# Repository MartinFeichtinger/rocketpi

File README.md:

# RocketPi
The aim of this project is to controll a water rocket with a Raspberry Pi Zero.

## What is a water rocket?
A water rocket is a type of model rocket using water as its reaction mass.
The water is forced out by a pressurized gas, typically compressed air. Like all rocket engines, it operates on the principle of Newton's third law of motion.

## What's special about our water rocket?
The fuel tank consists of a plastic bottle. This bottle can withstand a maximum pressure of 9 bar.
In order to achieve a higher flight altitude, we have decided to strengthen this plastic bottle with fiber-reinforced tape.
Whith this new tank we are able to reach pressures up to 13 bar.
Futhermore a Raspberry Pi Zero is used to eject the parachute and determine the flight altitude.
The parachute is attached to the top of the water rocket. To eject the parachute, the pre-tensioned handle is opened with three servo motors.
-image of the water rocket

## Rocket launcher

The rocket launcher had already been built beforehand. It also allows the rocket to be filled. Two ball valves can be used to switch between water and compressed air. The water rockets can then be launched by pulling a string.

## Rocketpi

### Raspberry Pi Zero
The Raspberry Pi Zero is a tiny, affordable computer board developed by the Raspberry Pi Foundation. It's small but powerful, with features like a CPU, RAM, storage, and ports for connecting to displays and other devices. It's used for various projects like IoT, robotics, and gaming consoles due to its low cost and versatility.

### BerryIMUv4
IMU stands for Inertial Measurement Unit. It's a device that measures and reports specific forces like acceleration and angular velocity, using a combination of accelerometers, gyroscopes, and sometimes magnetometers. IMUs are commonly used in applications like navigation systems, robotics, virtual reality, and motion tracking. They provide essential data for determining an object's orientation, position, and movement in 3D space.

The BerryIMUv4 is an IMU that was specially developed for the rasberry pi zero. In addition to acceleration, rotation rate and magnetic field, it is possible to measure barometric altitude and temperature. Furthermore, there is a GPS module for position determination.

For more inforations visit: https://ozzmaker.com/product/berrygps-imu/

Example Programms: https://github.com/ozzmaker/BerryIMU

### Power Board
The power board connects the Raspberry Pi to the lithium battery and the servo motors. It also acts as a bridge between the Raspberry Pi and the BerryIMUv4 sensor module, and between the Raspberry Pi and the control panel.

#### Schematic

#### PCB layout

### Controll Panel
The control panel enables interaction with the Raspberry Pi. On the one hand, control signals can be sent to the Raspberry Pi via a button, and on the other hand, the status of the Raspberry Pi can be displayed via LEDs. The entire system is switched on with a power switch. To signal that the Raspberry Pi is booting, a flashing signal is generated via a 555 timer. Immediately after the boot process, the reset input of the 555 timer is triggered and the boot LED stops flashing and remains lit. 

#### Schematic

#### PCB layout

## Software
### State-Machine

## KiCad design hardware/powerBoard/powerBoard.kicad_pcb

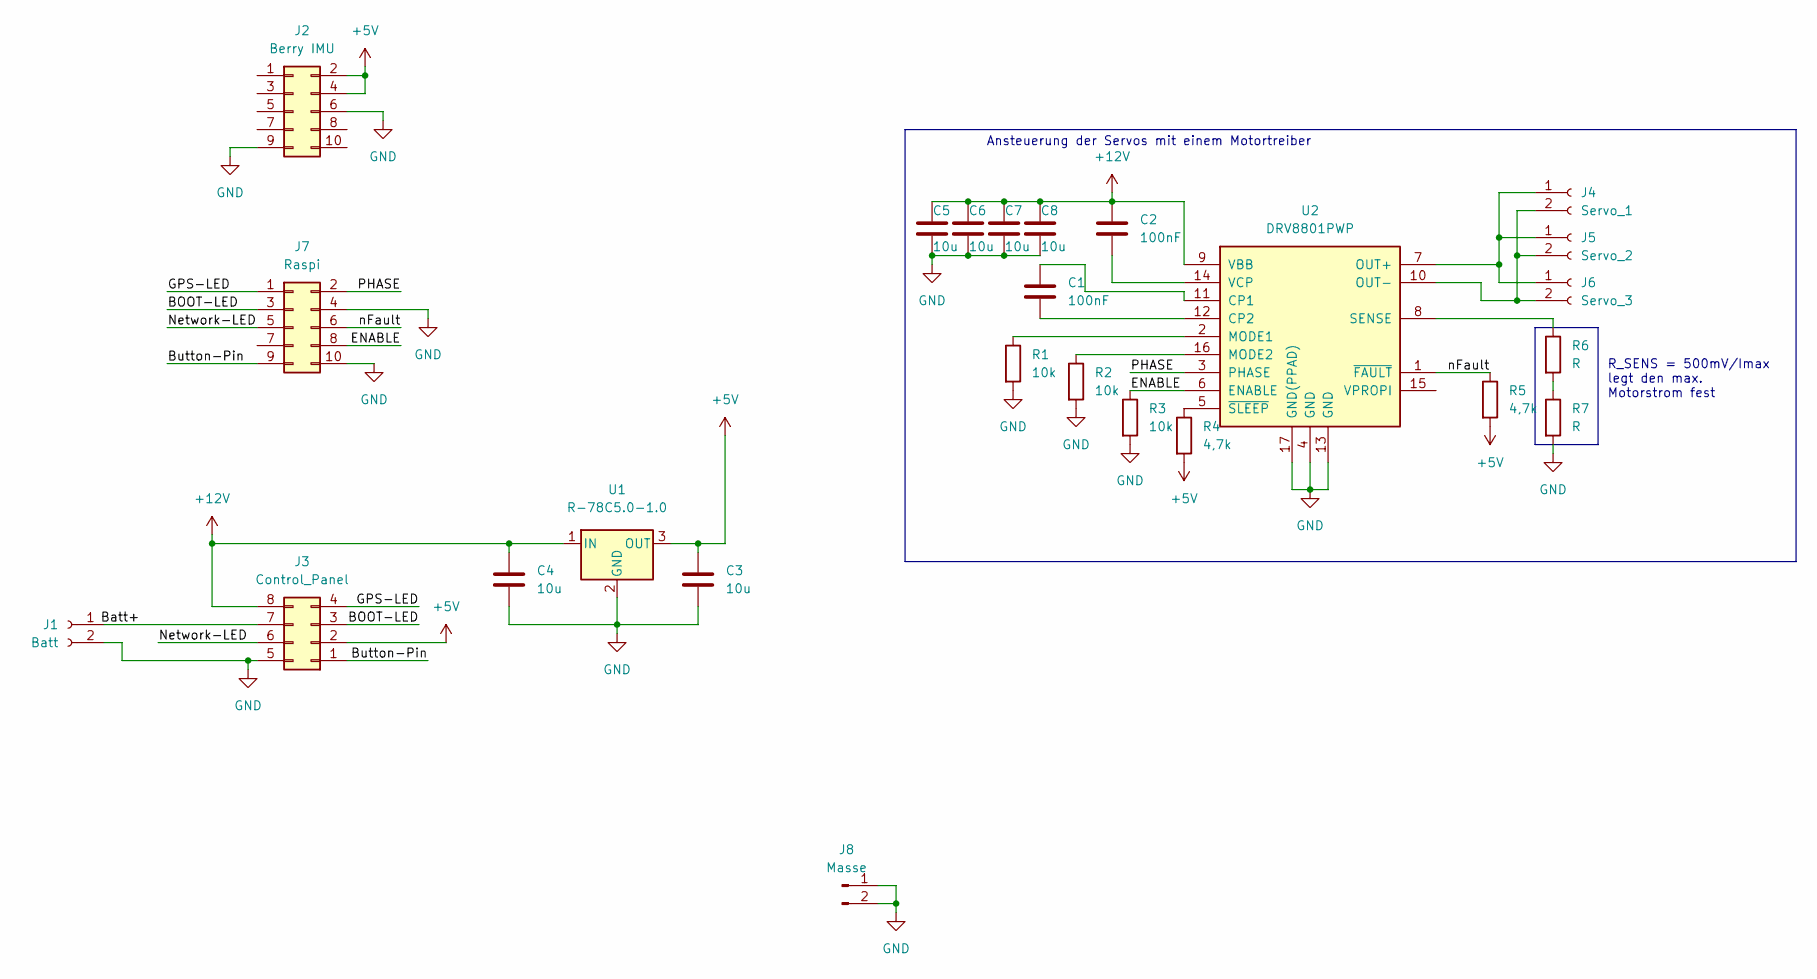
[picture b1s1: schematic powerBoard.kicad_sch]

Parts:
C1, C2: 100nF; C_0805_2012Metric_Pad1.18x1.45mm_HandSolder
C3, C4, C5, C6, C7, C8: 10u; C_0805_2012Metric_Pad1.18x1.45mm_HandSolder
J1: Batt; Pfusch_Conn
J2: Berry IMU; PinSocket_2x05_P2.54mm_Vertical
J3: Control_Panel; IDC-Header_2x04_P2.54mm_Vertical
J4: Servo_1; Pfusch_Conn
J5: Servo_2; Pfusch_Conn
J6: Servo_3; Pfusch_Conn
J7: Raspi; PinSocket_2x05_P2.54mm_Vertical
J8: Masse; PinHeader_1x02_P2.54mm_Vertical
R1, R2, R3: 10k; R_0805_2012Metric_Pad1.20x1.40mm_HandSolder
R4, R5: 4,7k; R_0805_2012Metric_Pad1.20x1.40mm_HandSolder
R6, R7: R; R_0805_2012Metric_Pad1.20x1.40mm_HandSolder
U1: R-78C5.0-1.0; Converter_DCDC_RECOM_R-78E-0.5_THT
U2: DRV8801PWP; HTSSOP-16-1EP_4.4x5mm_P0.65mm_EP3.4x5mm_Mask3x3mm_ThermalVi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

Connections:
+5V: C3.1, J2.2, J2.4, J3.2, R4.2, R5.2, U1.3 (OUT); also elsewhere on the board
+12V: C2.1, C4.1, C5.1, C6.1, C7.1, C8.1, J3.8, U1.1 (IN), U2.9 (VBB)
/BOOT-LED: J3.3, J7.3
/Batt+: J1.1, J3.7
/Button-Pin: J3.1, J7.9
/ENABLE: J7.8, R3.1, U2.6 (ENABLE)
/GPS-LED: J3.4, J7.1
/Network-LED: J3.6, J7.5
/PHASE: J7.2, U2.3 (PHASE)
/nFault: J7.6, R5.1, U2.1 (~FAULT)
GND: C3.2, C4.2, C5.2, C6.2, C7.2, C8.2, J1.2, J2.6, J2.9, J3.5, J7.4, J7.10, J8.1, J8.2, R1.2, R2.2, R3.2, R7.2, U1.2 (GND), U2.4 (GND), U2.13 (GND), U2.17 (GND(PPAD)); also elsewhere on the board
unnamed: C1.1, U2.11 (CP1)
unnamed: C1.2, U2.12 (CP2)
unnamed: C2.2, U2.14 (VCP)
unnamed: J4.1, J5.1, J6.1, U2.7 (OUT+)
unnamed: J4.2, J5.2, J6.2, U2.10 (OUT-)
unnamed: R1.1, U2.2 (MODE1)
unnamed: R2.1, U2.16 (MODE2)
unnamed: R4.1, U2.5 (~SLEEP)
unnamed: R6.1, U2.8 (SENSE)
unnamed: R6.2, R7.1

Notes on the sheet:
R_SENS = 500mV/Imax legt den max. Motorstrom fest
Ansteuerung der Servos mit einem Motortreiber

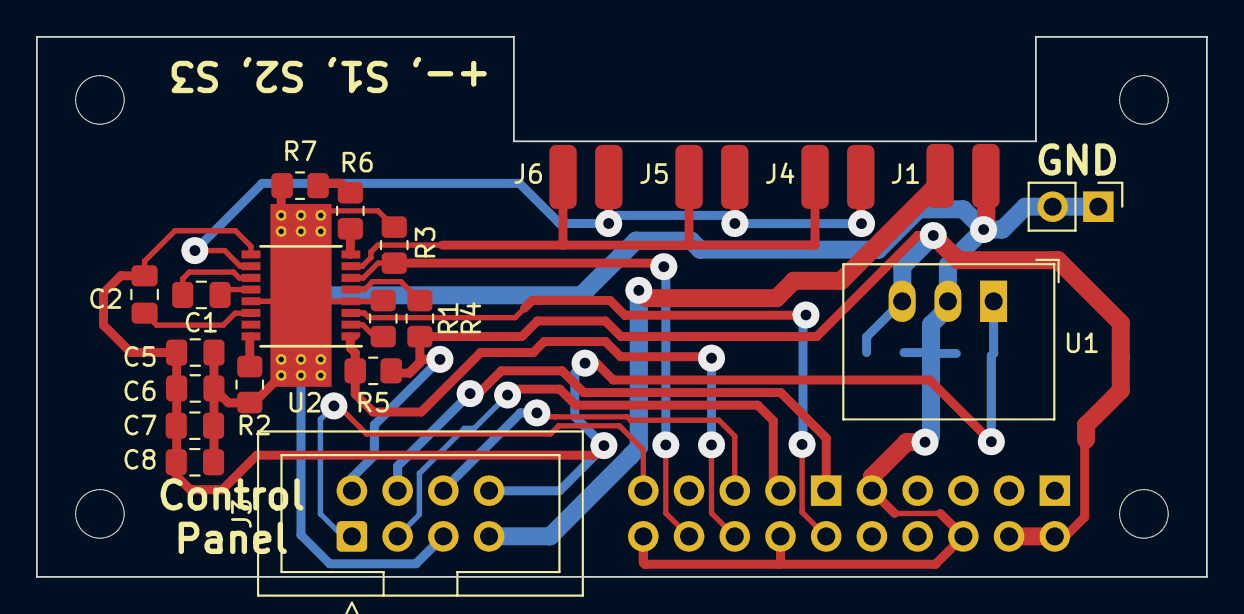
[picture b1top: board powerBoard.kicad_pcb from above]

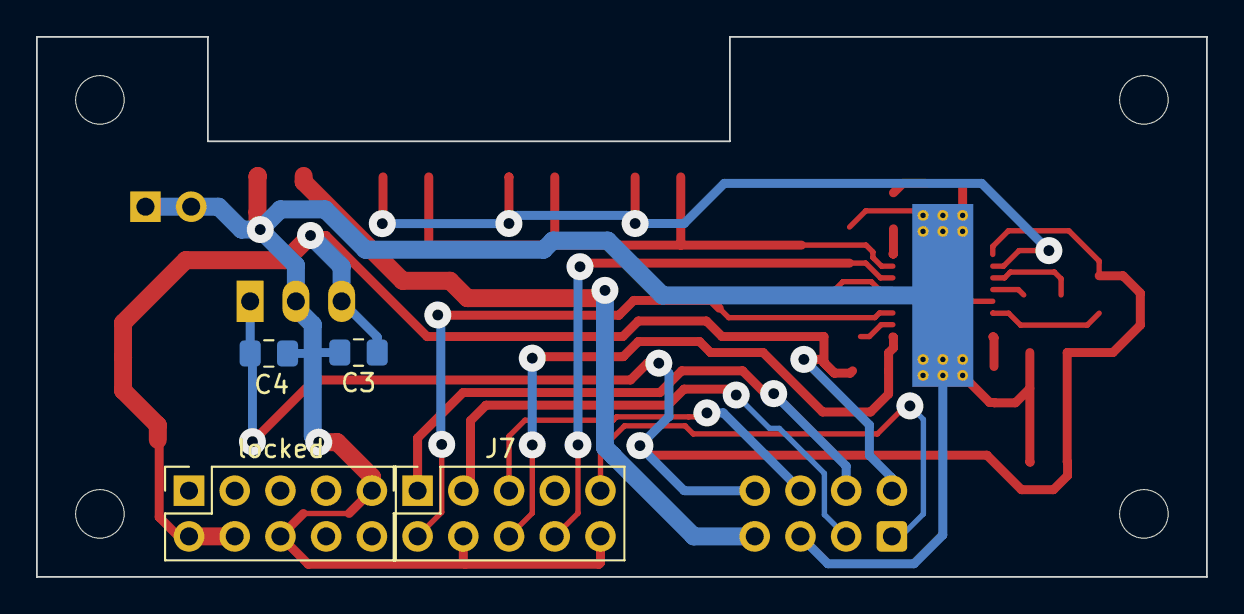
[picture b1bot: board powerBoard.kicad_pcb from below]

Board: 2 copper layers, 65.0 x 30.0 mm, 25 parts (4 on the bottom side), 21 nets.

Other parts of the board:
locked: Berry IMU; PinSocket_2x05_P2.54mm_Vertical

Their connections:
+5V: locked.2, locked.4; also elsewhere on the board
GND: locked.6, locked.9; also elsewhere on the board

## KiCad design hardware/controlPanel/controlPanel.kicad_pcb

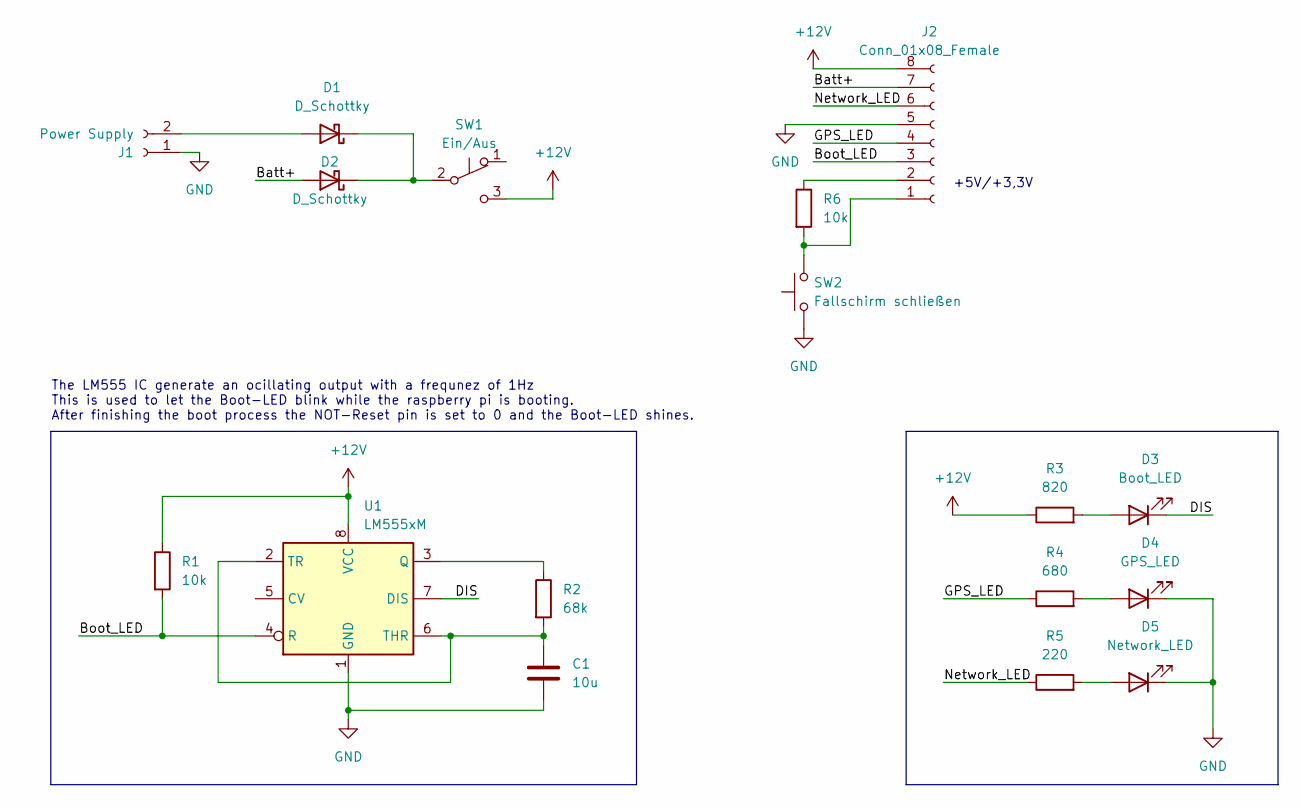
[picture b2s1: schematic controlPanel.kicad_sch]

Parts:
C1: 10u; C_1206_3216Metric_Pad1.33x1.80mm_HandSolder
D1, D2: D_Schottky; D_SMA_Handsoldering
D3: Boot_LED; LED_D3.0mm
D4: GPS_LED; LED_D3.0mm
D5: Network_LED; LED_D3.0mm
J1: Power Supply; PhoenixContact_MCV_1,5_2-G-5.08_1x02_P5.08mm_Vertical
J2: Conn_01x08_Female; PinHeader_1x08_P2.00mm_Vertical
R1, R6: 10k; R_1206_3216Metric_Pad1.30x1.75mm_HandSolder
R2: 68k; R_1206_3216Metric_Pad1.30x1.75mm_HandSolder
R3: 820; R_1206_3216Metric_Pad1.30x1.75mm_HandSolder
R4: 680; R_1206_3216Metric_Pad1.30x1.75mm_HandSolder
R5: 220; R_1206_3216Metric_Pad1.30x1.75mm_HandSolder
SW1: Ein/Aus; slide_switch
SW2: Fallschirm schließen; SW_Push_1P1T_NO_6x6mm_H9.5mm
U1: LM555xM; DIP-8_W7.62mm_Socket_LongPads

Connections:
+12V: J2.8, R1.1, R3.1, SW1.3 (C), U1.8 (VCC)
/Batt+: D2.2 (A), J2.7
/Boot_LED: J2.3, R1.2, U1.4 (R)
/DIS: D3.1 (K), U1.7 (DIS)
/GPS_LED: J2.4, R4.1
/Network_LED: J2.6, R5.1
GND: C1.2, D4.1 (K), D5.1 (K), J1.1, J2.5, SW2.1, U1.1 (GND)
unnamed: C1.1, R2.2, U1.2 (TR), U1.6 (THR)
unnamed: D1.1 (K), D2.1 (K), SW1.2 (B)
unnamed: D1.2 (A), J1.2
unnamed: D3.2 (A), R3.2
unnamed: D4.2 (A), R4.2
unnamed: D5.2 (A), R5.2
unnamed: J2.1, R6.2, SW2.2
unnamed: J2.2, R6.1
unnamed: R2.1, U1.3 (Q)

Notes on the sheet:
+5V/+3,3V
The LM555 IC generate an ocillating output with a frequnez of 1Hz This is used to let the Boot-LED blink while the raspberry pi is booting. After finishing the boot process the NOT-Reset pin is set to 0 and the Boot-LED shines.

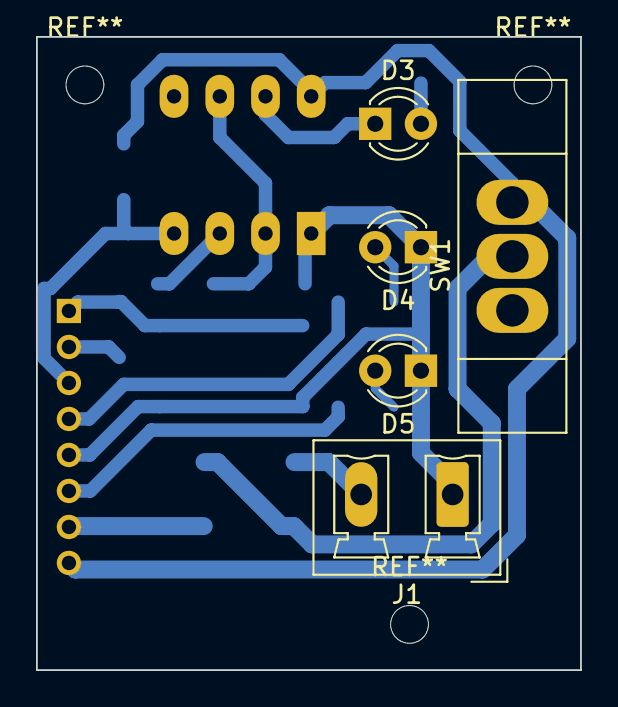
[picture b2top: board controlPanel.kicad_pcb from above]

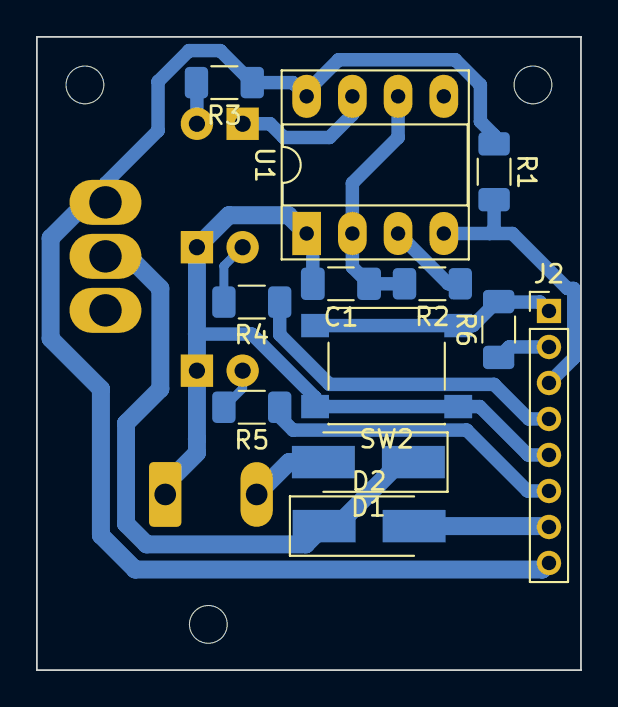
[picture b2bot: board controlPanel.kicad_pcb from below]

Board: 2 copper layers, 30.2 x 35.2 mm, 17 parts (12 on the bottom side), 16 nets.

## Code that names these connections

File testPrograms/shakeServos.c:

#include <stdio.h>
#include <stdbool.h>
#include <pigpiod_if2.h>

// powerBoard
#define ENABLE		24
#define PHASE		18
#define NFAULT		23

// controlPanel
#define GPS_LED		17
#define BOOT_LED	27
#define NET_LED		22
#define BUTTON		10


void nfault_cb(int pi, unsigned user_gpio, unsigned edge, uint32_t tick);
void button_cb(int pi, unsigned user_gpio, unsigned edge, uint32_t tick);

bool shaking=false;

int main(){
	////////////////////////// INIT GPIO SETTINGS //////////////////////////
	// init gpio client
	const int pi = pigpio_start(NULL, NULL);
	if(pi < 0){
		printf("Raspberry Pi not found");
		return -1;
	}

	// init gpios
	set_mode(pi, ENABLE, PI_OUTPUT);
	set_mode(pi, PHASE, PI_OUTPUT);
	set_mode(pi, NFAULT, PI_INPUT);

	set_mode(pi, GPS_LED, PI_OUTPUT);
	set_mode(pi, BOOT_LED, PI_OUTPUT);
	set_mode(pi, NET_LED, PI_OUTPUT);
	set_mode(pi, BUTTON, PI_INPUT);

	// init button spefic gpio settings
	set_glitch_filter(pi, BUTTON, 20000);	// ingor all input changes for 20ms after the input state changes
	const int cb_id = callback(pi, BUTTON, EITHER_EDGE, button_cb);
	if(cb_id < 0){
		printf("init callback failed");
		return -1;
	}

	// cofigurate the pwm
	int pwm_frequency = 8000;
	int real_pwm_frequency = set_PWM_frequency(pi, ENABLE, pwm_frequency);
	printf("pwm_frequency: set=%d; real=%d\n", pwm_frequency, real_pwm_frequency);

	int pwm_range = 25;
	int real_pwm_range = set_PWM_range(pi, ENABLE, pwm_range);	// => 1 = 1%
	printf("pwm_range: set=%d; real=%d\n", pwm_range, real_pwm_range);

	// init NFAULT callback function
	const int nfault_cb_id = callback(pi, NFAULT, EITHER_EDGE, nfault_cb);
	if(nfault_cb_id < 0){
		printf("init callback failed");
		return -1;
	}

	////////////////////////// START OF THE REAL SHIT //////////////////////////
	gpio_write(pi, BOOT_LED, 0);

	while(1){
		if(shaking){
			set_PWM_dutycycle(pi, ENABLE, 10);
			gpio_write(pi, PHASE, 0);
			time_sleep(0.07);
			gpio_write(pi, PHASE, 1);
			time_sleep(0.07);
		}
		else{
			set_PWM_dutycycle(pi, ENABLE, 0);
		}
	}
}

void nfault_cb(int pi, unsigned user_gpio, unsigned edge, uint32_t tick){
	if(edge == FALLING_EDGE){
		printf("nFault turned LOW\n");
		gpio_write(pi, NET_LED, 1);
	}
	else if(edge == RISING_EDGE){
		printf("nFault turned HIGH\n");
		gpio_write(pi, NET_LED, 0);
	}
	else{
		printf("some wierd timeout occured\n");
	}
}

void button_cb(int pi, unsigned user_gpio, unsigned edge, uint32_t tick){
	if(edge == RISING_EDGE){
		gpio_write(pi, GPS_LED, 1);
		shaking=true;
		printf("Button pressed\n");
	}
	else if(edge == FALLING_EDGE){
		gpio_write(pi, GPS_LED, 0);
		shaking=false;
		printf("Button released\n");
	}
}

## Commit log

2024-04-14 Added the example Repo for the berry IMUv4
2024-04-14 Added folder with the relvant berry IMUv4 examples
2024-04-14 Added a setup guide for the rocketpi (Raspberry Pi Zero W / 2W)
2024-04-17 Fixed typo in README.md
2024-04-20 cleaned the repo
2024-04-20 added the kiCad schematics
2024-05-04 added gpio configuration
2024-05-04 started the pigpio docu
2024-05-04 added a picture of the raspbery pis pinout
2024-05-04 added a blink test programm
2024-05-04 fixed some bugs at the pigpioTest programm
2024-05-09 added a test programm for the modified servo motors and changed spaces to tabs
2024-05-14 changed the footprint of the connector to the controlPanel and changed the order of the pin numbers
2024-05-14 added function void msleep() to use instead of usleep()
2024-05-14 added a test programm for the leds on the controlPanel
2024-05-14 added a test programm for the button
2024-05-16 improved the servo test programm
2024-05-16 added callback_cancel()
2024-05-18 fixed some bugs in the servoTest.c program
2024-05-18 improved the ledTest.c programm
2024-05-18 fixed the button test programm
2024-05-18 added a programm to test the servos controlled with the button
2024-05-18 fixed some bugs
2024-05-21 added a test programm for the mpu6050. changed a programm name
2024-05-25 fixed some bugs in the mpu6050 test programm
2024-05-25 added some stuff
2024-05-25 added a test program to make the servos shaking ;)
2024-05-25 added instuctions to config the boot led
2024-05-25 removed berry imu test examples
2024-05-26 started the rocketpi.c programm
2024-05-26 fixed some small bugs in rocketpi.c
2024-05-26 added a diagramm
2024-05-28 fixed cirtical bug
2024-05-28 added a signal handler to catch ctrl+c
2024-05-30 added file storage to the test programm
2024-05-31 fixed some small bugs
2024-05-31 cleaned the code a little bit
2024-05-31 added instructions to use files with pigpio
2024-05-31 fixed some bug at saving the file
2024-05-31 bend over thats a big one
2024-06-01 Refactor code to improve file handling and add signal handler
2024-06-01 tried to fix some bugs
2024-06-01 fixd stupid bug
2024-06-01 fixed bug
2024-06-01 fixed small bugs
2024-06-01 fixed smal bugs
2024-06-01 rocketpi.c is running
2024-06-01 improved the accereration stuff
2024-06-01 finished state for tomorrow
2024-07-06 small changes
2024-08-10 added instructions to set up your local time
2024-08-28 some changes
2024-08-28 added a c test programm to check internet connection
